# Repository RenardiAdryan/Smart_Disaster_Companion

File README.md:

# Smart_Disaster_Companion

This project is aimed to provide early warning system for fire.
it has IOT system that connect to the server, so users can know where the fire occured.
This thing will be connected with web application VIA firebase.com

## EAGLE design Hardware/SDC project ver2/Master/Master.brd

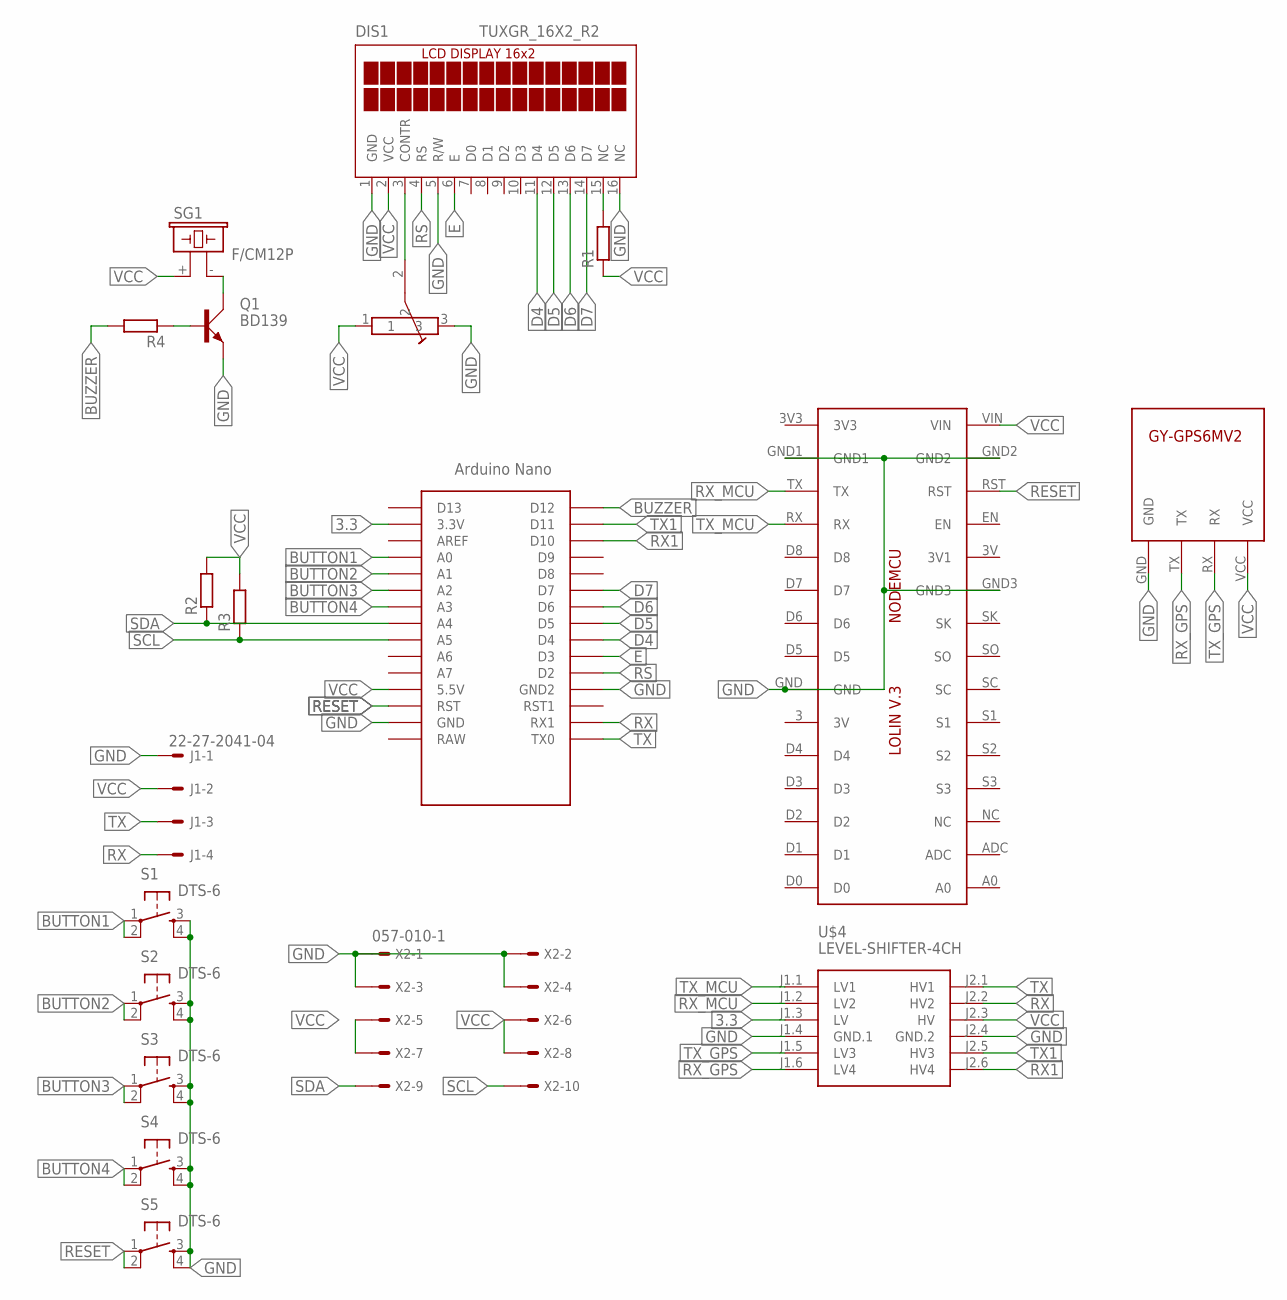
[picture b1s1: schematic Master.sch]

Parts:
DIS1: TUXGR_16X2_R2
IC1: LOLINV3
J1: 22-27-2041-04; 6410-04
Q1: BD139; TO126AV
R1, R2, R3, R4: R-EU_M0805; M0805
S1, S2, S3, S4, S5: DTS-6
SG1: F/CM12P
U$1: NANO
U$2: TRIMPOT
U$4: LEVEL-SHIFTER-4CH
U$5: GY-GPS6MV2
X2: 057-010-1

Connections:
3.3: U$1.3.3V, U$4.J1.3 (LV)
BUTTON1: S1.1, S1.2, U$1.A0
BUTTON2: S2.1, S2.2, U$1.A1
BUTTON3: S3.1, S3.2, U$1.A2
BUTTON4: S4.1, S4.2, U$1.A3
BUZZER: R4.2, U$1.D12
D4: DIS1.11 (D4), U$1.D4
D5: DIS1.12 (D5), U$1.D5
D6: DIS1.13 (D6), U$1.D6
D7: DIS1.14 (D7), U$1.D7
E: DIS1.6 (E), U$1.D3
GND: DIS1.1 (GND), DIS1.5 (R/W), DIS1.16 (NC), IC1.GND, IC1.GND1, IC1.GND2, IC1.GND3, J1.1, Q1.E, S1.3, S1.4, S2.3, S2.4, S3.3, S3.4, S4.3, S4.4, S5.3, S5.4, U$1.GND, U$1.GND1 (GND2), U$2.3, U$4.J1.4 (GND.1), U$4.J2.4 (GND.2), U$5.GND, X2.1, X2.2, X2.3, X2.4
unnamed: DIS1.3 (CONTR), U$2.2
unnamed: DIS1.15 (NC), R1.2
unnamed: Q1.B, R4.1
unnamed: Q1.C, SG1.- (2)
RESET: IC1.RST, S5.1, S5.2, U$1.RST
RS: DIS1.4 (RS), U$1.D2
RX: J1.4, U$1.RX1, U$4.J2.2 (HV2)
RX1: U$1.D10, U$4.J2.6 (HV4)
RX_GPS: U$4.J1.6 (LV4), U$5.TX
RX_MCU: IC1.TX, U$4.J1.2 (LV2)
SCL: R3.1, U$1.A5, X2.10
SDA: R2.1, U$1.A4, X2.9
TX: J1.3, U$1.TX0, U$4.J2.1 (HV1)
TX1: U$1.D11, U$4.J2.5 (HV3)
TX_GPS: U$4.J1.5 (LV3), U$5.RX
TX_MCU: IC1.RX, U$4.J1.1 (LV1)
VCC: DIS1.2 (VCC), IC1.VIN, J1.2, R1.1, R2.2, R3.2, SG1.+ (1), U$1.5V (5.5V), U$2.1, U$4.J2.3 (HV), U$5.VCC, X2.5, X2.6, X2.7, X2.8

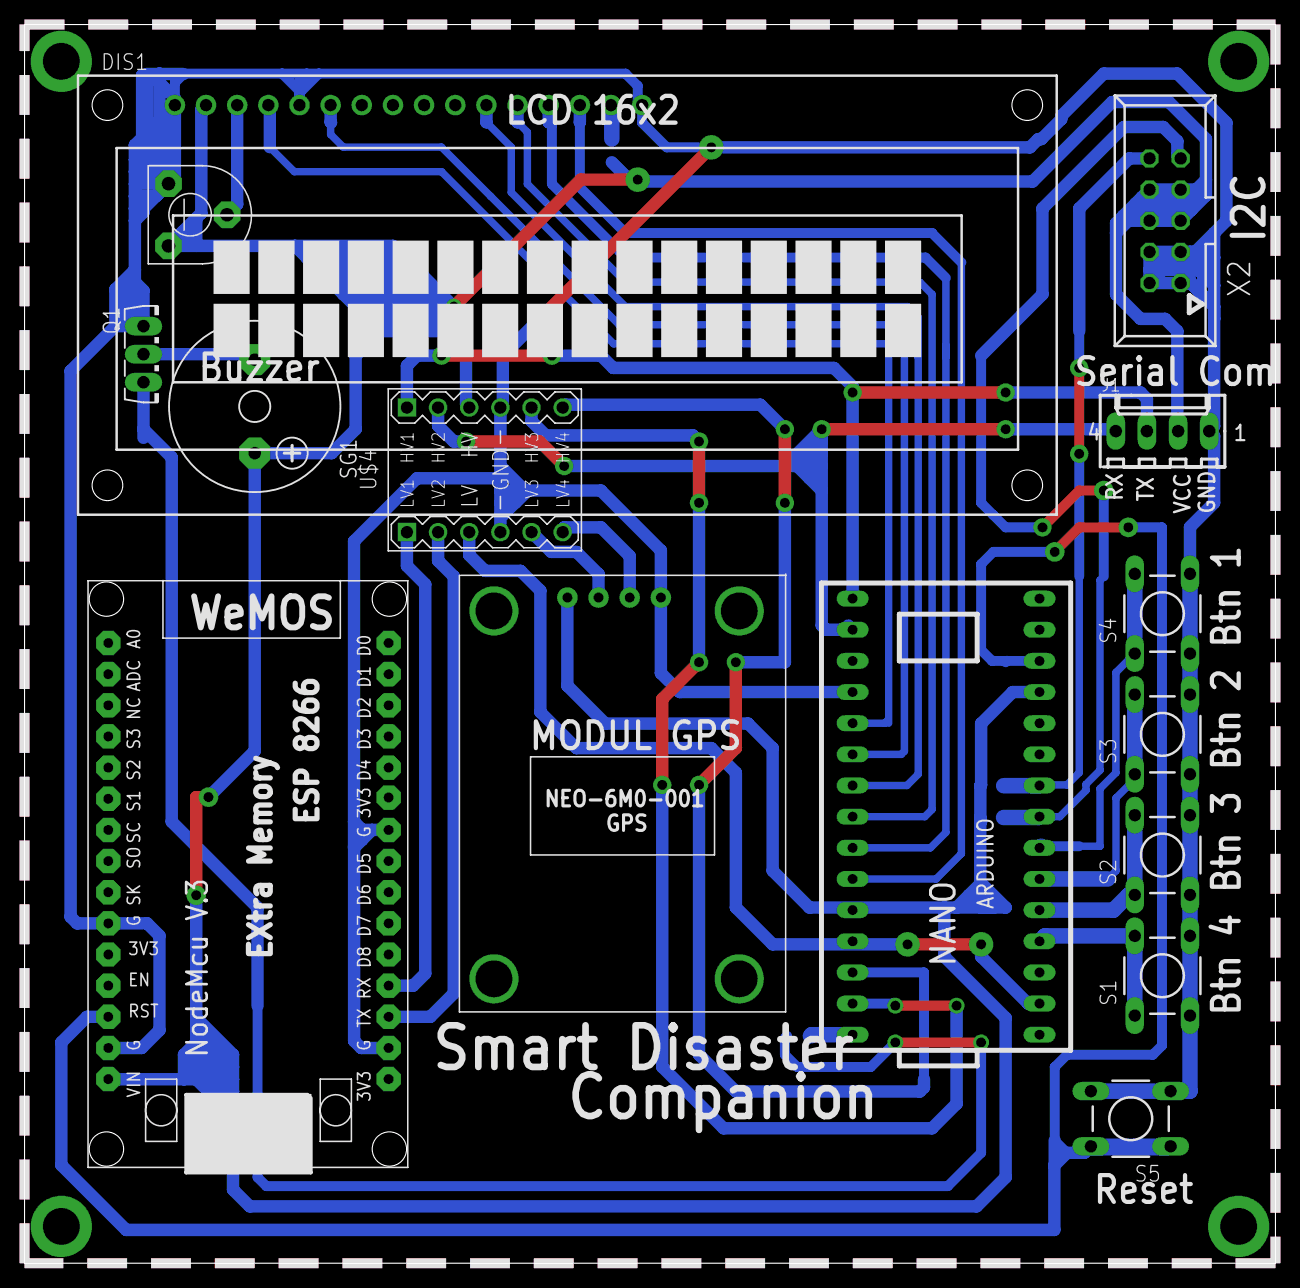
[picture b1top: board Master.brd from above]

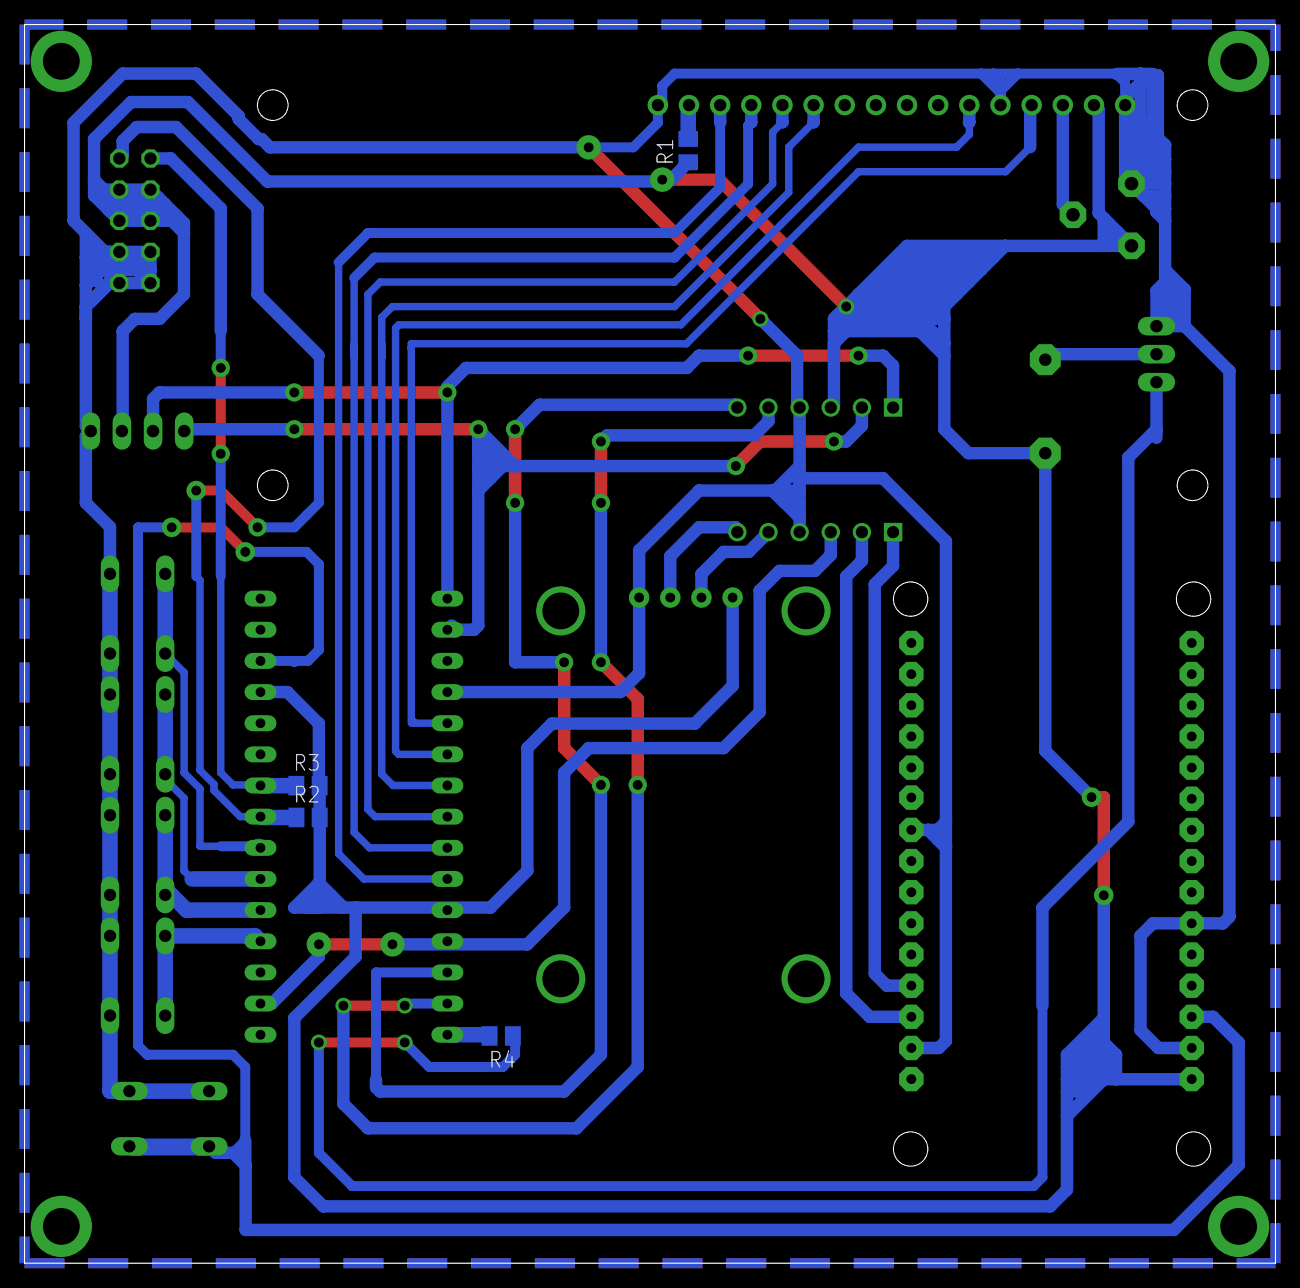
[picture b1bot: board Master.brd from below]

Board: 2 copper layers, 102.0 x 101.0 mm, 19 parts (4 on the bottom side), 29 nets.

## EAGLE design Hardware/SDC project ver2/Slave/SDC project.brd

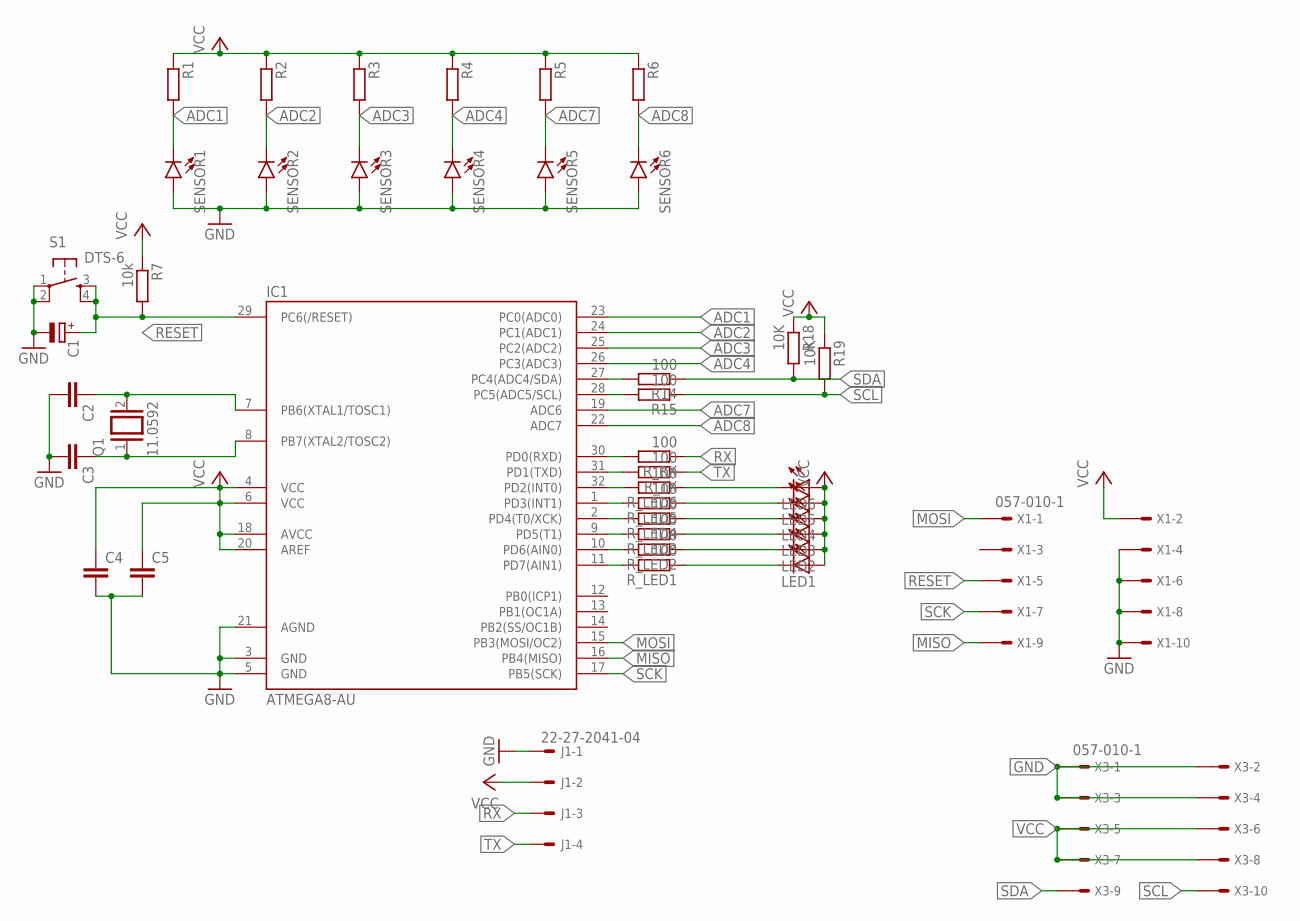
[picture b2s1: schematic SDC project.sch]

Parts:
C1: CPOL-EUE2.5-5; E2,5-5
C2, C3: C5/2.5; C5B2.5
C4, C5: C-EUC1206; C1206
IC1: ATMEGA8-AU; TQFP32-08
J1: 22-27-2041-04; 6410-04
LED1, LED2, LED3, LED4, LED5, LED6: LEDSML0805; SML0805
Q1: 11.0592; QS
R1, R2, R3, R4, R5, R6: R-EU_R0805; R0805
R7: 10k; R0805
R14, R15: 100; R0805
R18, R19: 10K; R0805
R_LED1, R_LED2, R_LED3, R_LED4, R_LED5, R_LED6: 100; R0805
R_RX: 100; R0805
R_TX: 100; R0805
S1: DTS-6
SENSOR1, SENSOR2, SENSOR3, SENSOR4, SENSOR5, SENSOR6: LED5MM; LED_5MM
X1, X3: 057-010-1

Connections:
ADC1: IC1.23 (PC0(ADC0)), R1.2, SENSOR1.K (C)
ADC2: IC1.24 (PC1(ADC1)), R2.2, SENSOR2.K (C)
ADC3: IC1.25 (PC2(ADC2)), R3.2, SENSOR3.K (C)
ADC4: IC1.26 (PC3(ADC3)), R4.2, SENSOR4.K (C)
ADC7: IC1.19 (ADC6), R5.2, SENSOR5.K (C)
ADC8: IC1.22 (ADC7), R6.2, SENSOR6.K (C)
GND: C1.-, C2.2, C3.2, C4.2, C5.2, IC1.3 (GND), IC1.5 (GND), IC1.21 (AGND), J1.1, S1.1, S1.2, SENSOR1.A, SENSOR2.A, SENSOR3.A, SENSOR4.A, SENSOR5.A, SENSOR6.A, X1.4, X1.6, X1.8, X1.10, X3.1, X3.2, X3.3, X3.4
MISO: IC1.16 (PB4(MISO)), X1.9
MOSI: IC1.15 (PB3(MOSI/OC2)), X1.1
unnamed: IC1.30 (PD0(RXD)), R_RX.2
unnamed: IC1.31 (PD1(TXD)), R_TX.2
unnamed: IC1.27 (PC4(ADC4/SDA)), R14.2
unnamed: C2.1, IC1.7 (PB6(XTAL1/TOSC1)), Q1.2
unnamed: C3.1, IC1.8 (PB7(XTAL2/TOSC2)), Q1.1
unnamed: IC1.28 (PC5(ADC5/SCL)), R15.2
unnamed: IC1.32 (PD2(INT0)), R_LED6.2
unnamed: IC1.1 (PD3(INT1)), R_LED5.2
unnamed: IC1.2 (PD4(T0/XCK)), R_LED4.2
unnamed: IC1.9 (PD5(T1)), R_LED3.2
unnamed: IC1.10 (PD6(AIN0)), R_LED2.2
unnamed: IC1.11 (PD7(AIN1)), R_LED1.2
unnamed: LED6.C, R_LED6.1
unnamed: LED5.C, R_LED5.1
unnamed: LED4.C, R_LED4.1
unnamed: LED3.C, R_LED3.1
unnamed: LED2.C, R_LED2.1
unnamed: LED1.C, R_LED1.1
RESET: C1.+, IC1.29 (PC6(/RESET)), R7.2, S1.3, S1.4, X1.5
RX: J1.3, R_RX.1
SCK: IC1.17 (PB5(SCK)), X1.7
SCL: R15.1, R19.2, X3.10
SDA: R14.1, R18.2, X3.9
TX: J1.4, R_TX.1
VCC: C4.1, C5.1, IC1.4 (VCC), IC1.6 (VCC), IC1.18 (AVCC), IC1.20 (AREF), J1.2, LED1.A, LED2.A, LED3.A, LED4.A, LED5.A, LED6.A, R1.1, R2.1, R3.1, R4.1, R5.1, R6.1, R7.1, R18.1, R19.1, X1.2, X3.5, X3.6, X3.7, X3.8

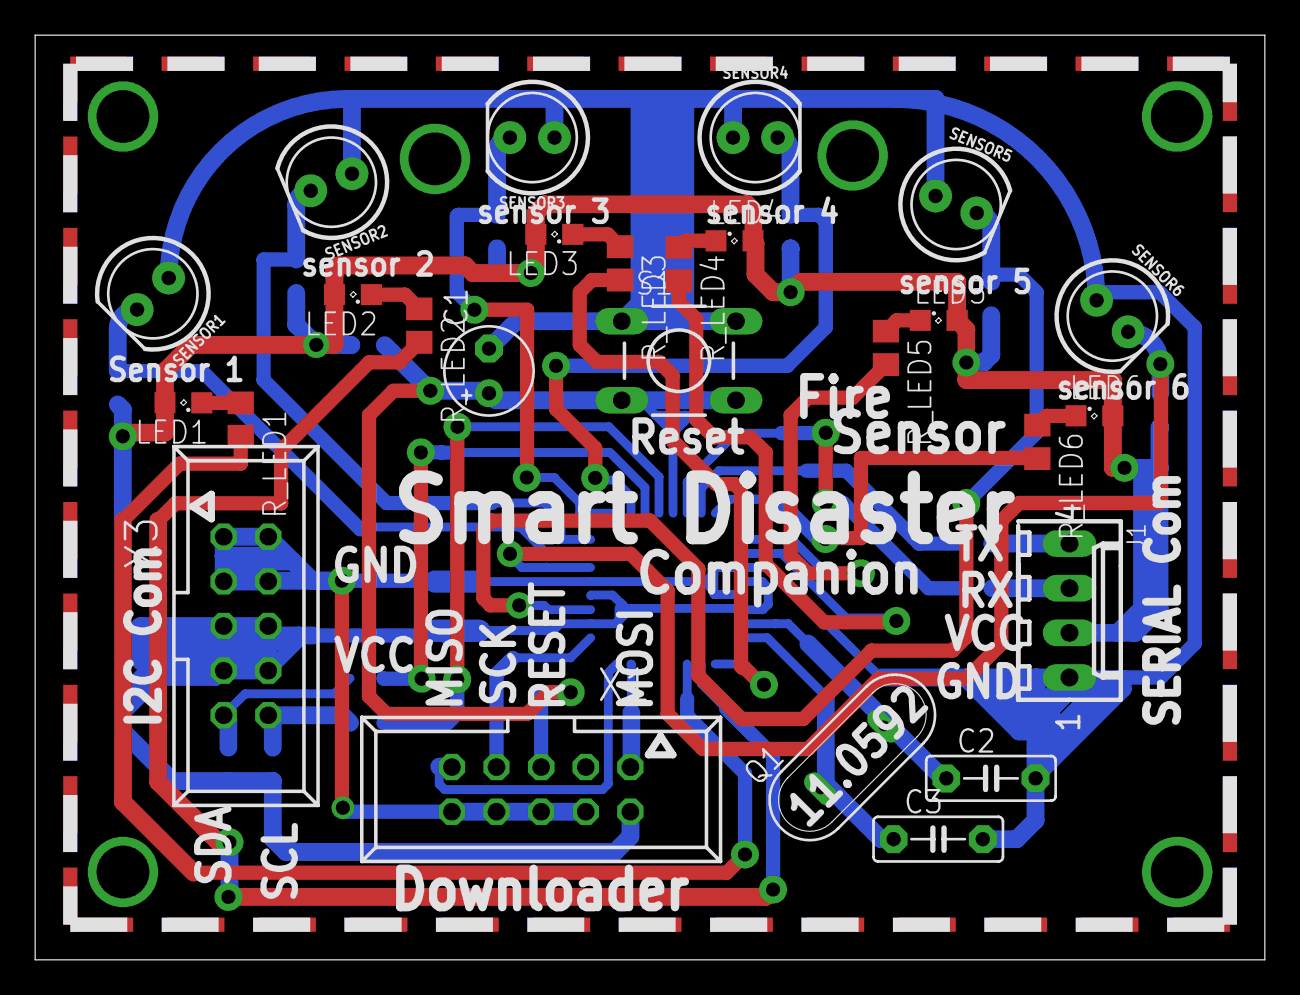
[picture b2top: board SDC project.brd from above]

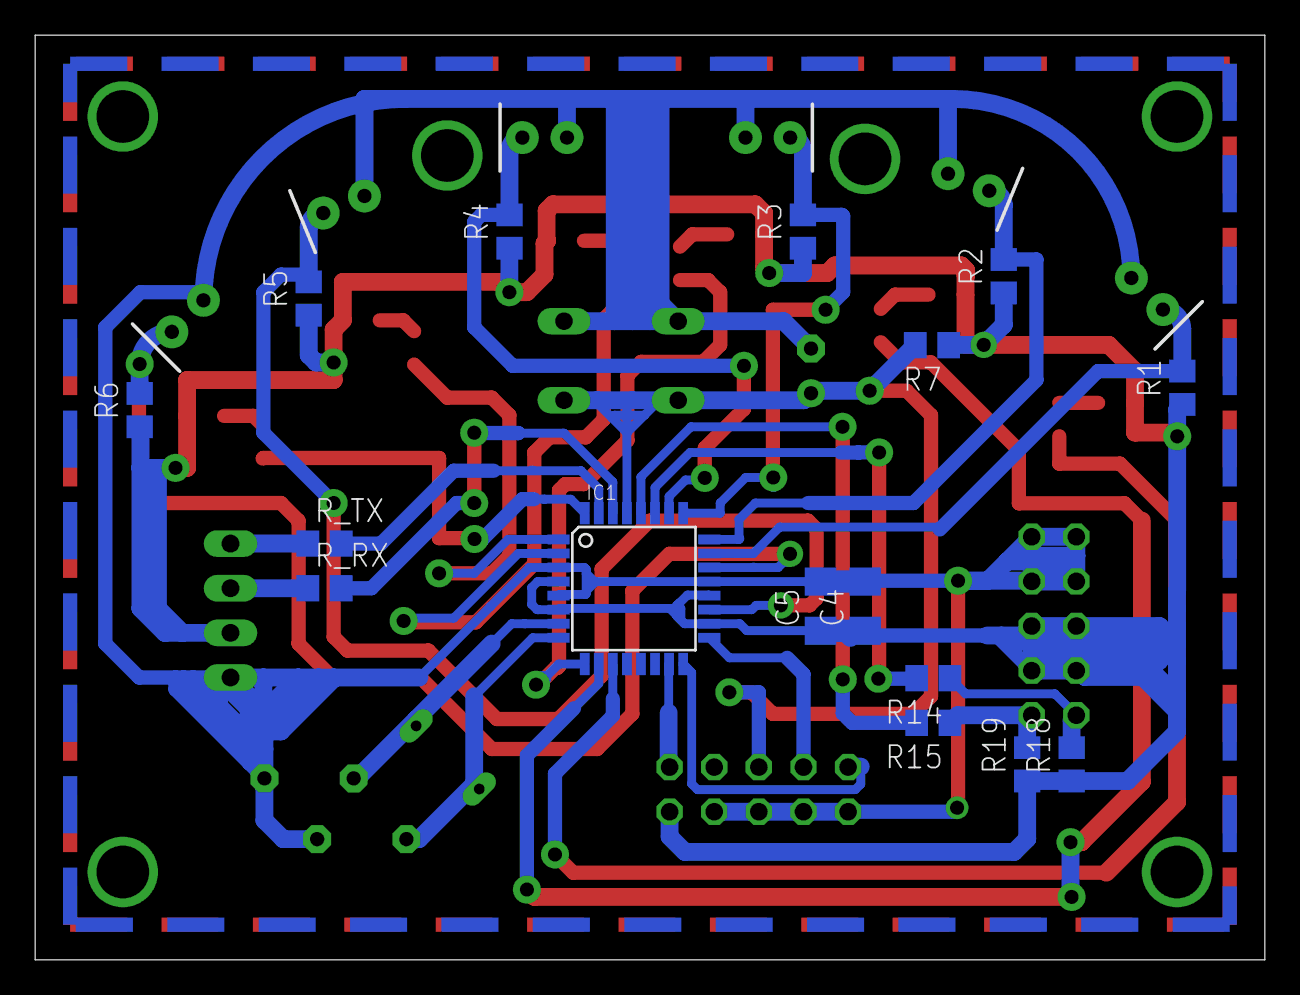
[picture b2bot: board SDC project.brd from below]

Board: 2 copper layers, 70.0 x 52.6 mm, 42 parts (16 on the bottom side), 34 nets.

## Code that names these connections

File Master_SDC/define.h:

#ifndef _DEFINE_H
#define _DEFINE_H

#include <SoftwareSerial.h> 
#include <TinyGPS++.h> 
#include <Wire.h>
#include <LiquidCrystal.h>
#include "pitches.h"
TinyGPSPlus gps; // create gps object 



const int rs = 2, en = 3, d4 = 4, d5 = 5, d6 = 6, d7 = 7;
LiquidCrystal lcd(rs, en, d4, d5, d6, d7);

SoftwareSerial gpsSerial(10,11);//rx,tx 

#define fireSensor2   0x25
#define fireSensor1   0x31
#define BUZZER_PIN 12
#define LEDBUILTIN 13

#define BUTTON4   A0
#define BUTTON3   A1
#define BUTTON2   A2
#define BUTTON1   A3




extern void GetGPS();
extern double latitude,longitude;
extern void Buzzer();
#endif

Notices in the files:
parts and their libraries:
GPS neo6mv2: Released under the Creative Commons Attribution 4.0 International License: http://creativecommons.org/licenses/by/4.0
SparkFun-LED: Licensing: Creative Commons ShareAlike 4.0 International - https://creativecommons.org/licenses/by-sa/4.0
